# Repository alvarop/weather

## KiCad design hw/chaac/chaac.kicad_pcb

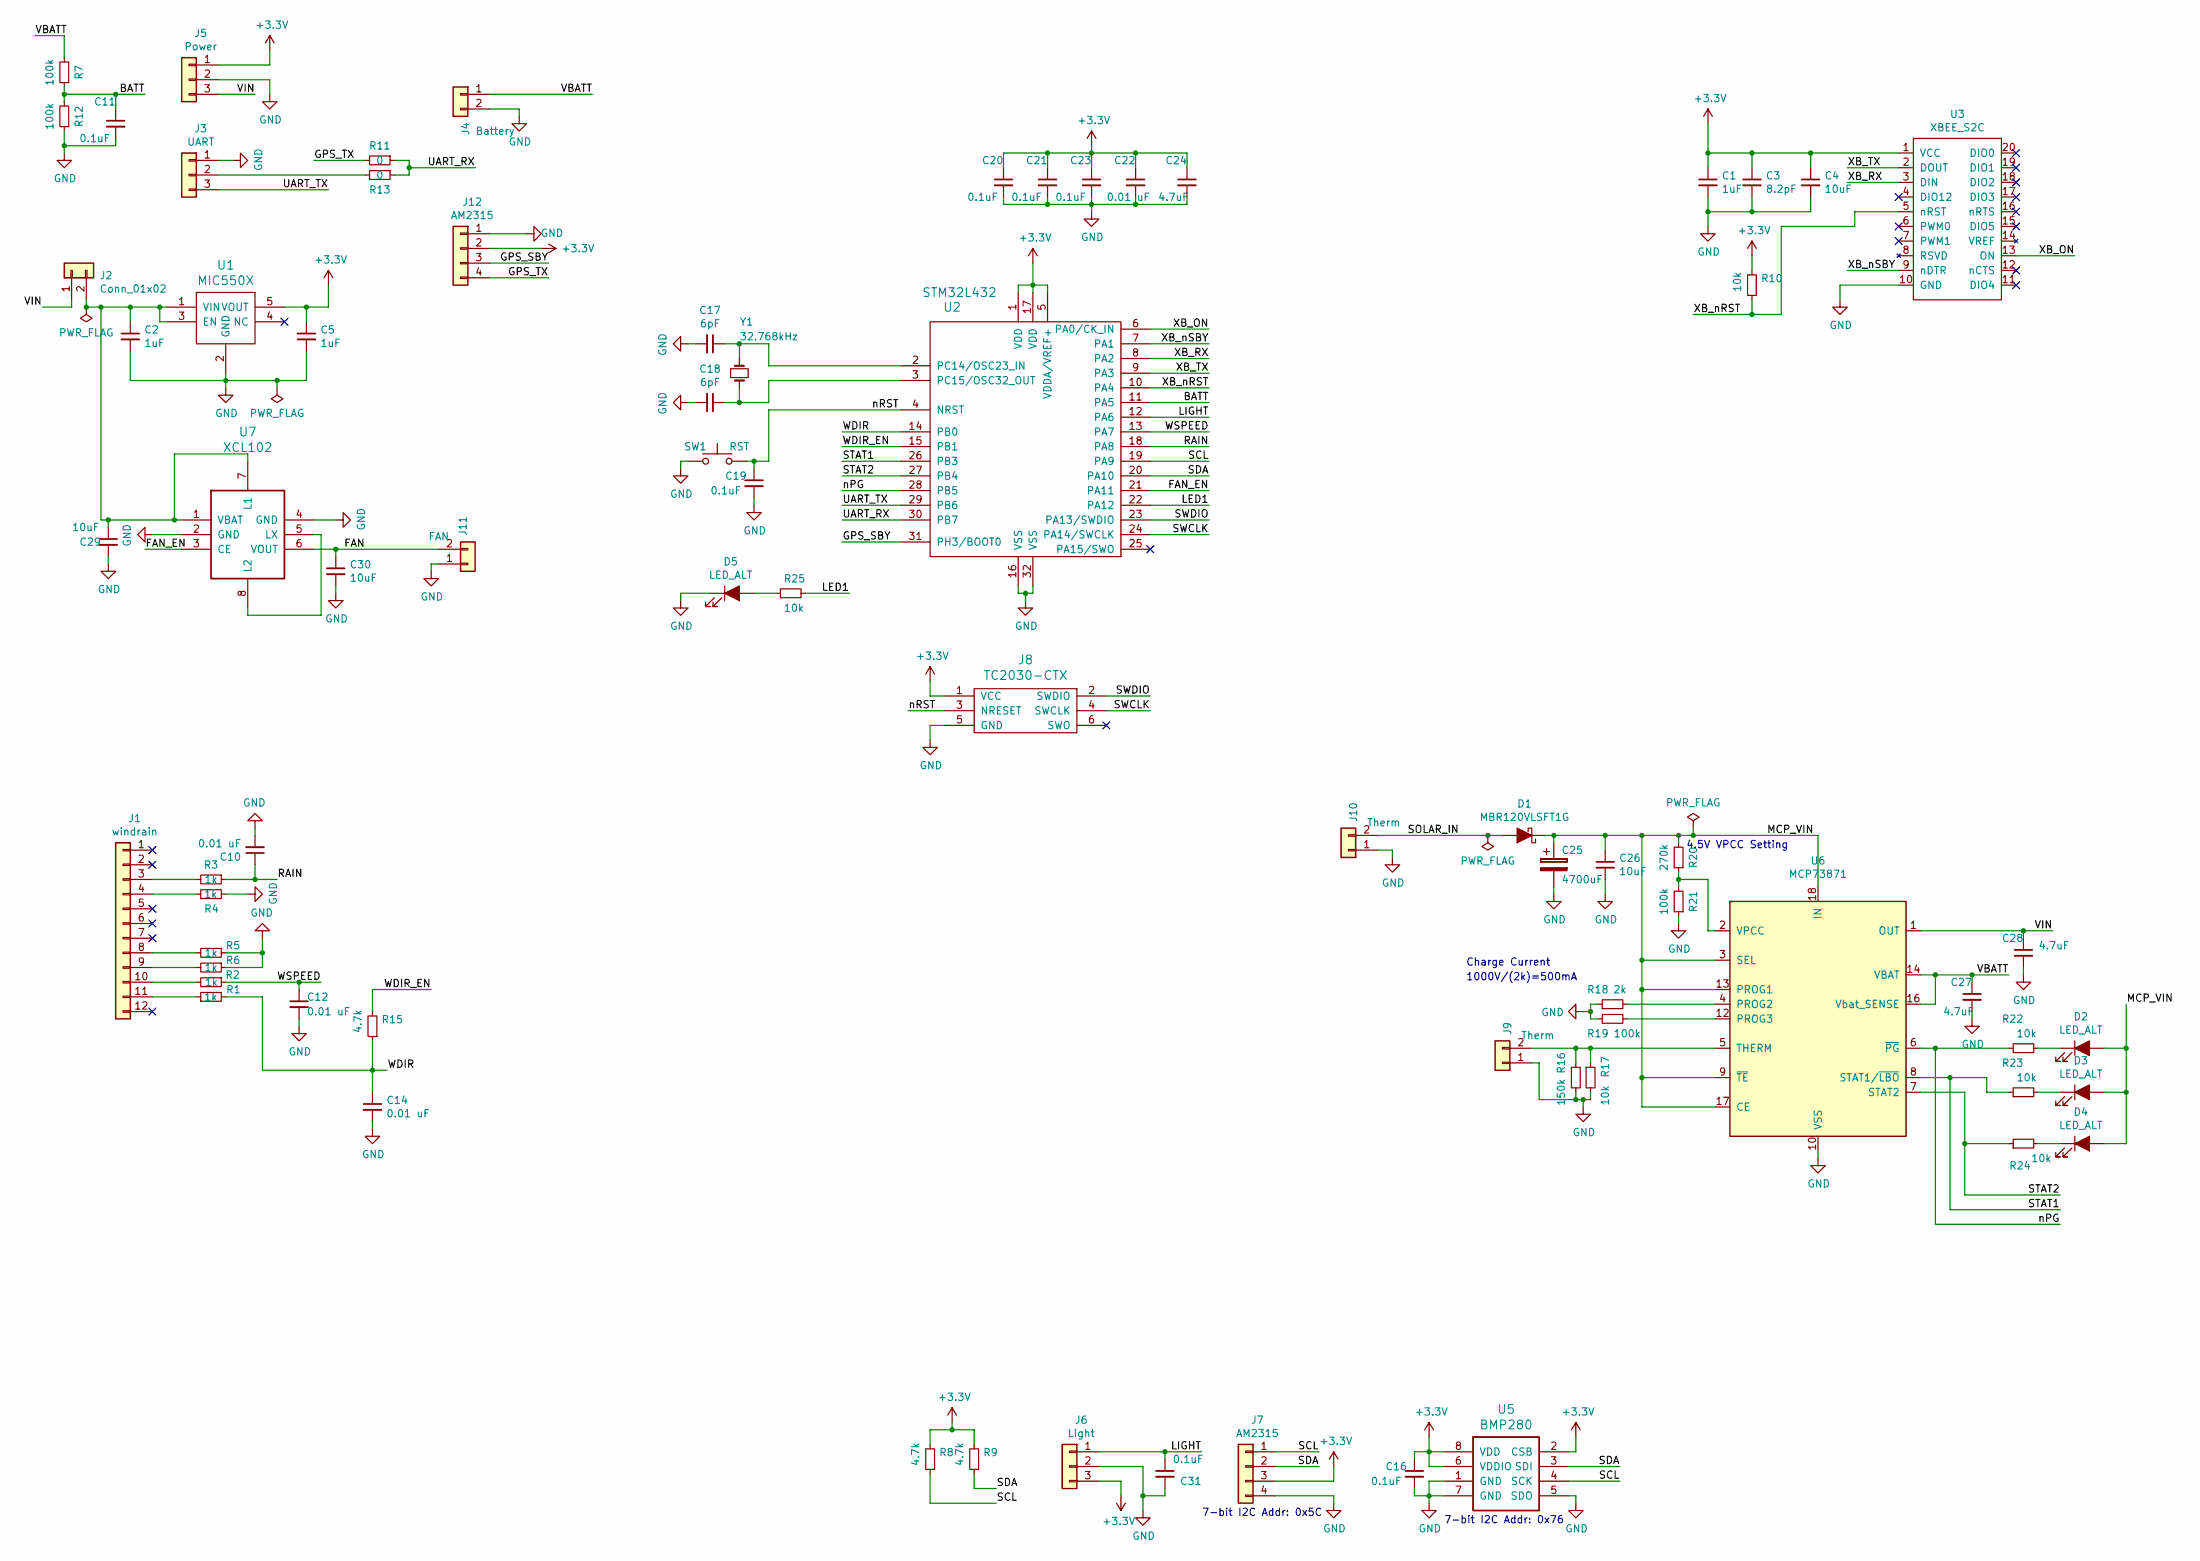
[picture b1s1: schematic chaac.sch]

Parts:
C1, C2, C5: 1uF; C_0603_1608Metric; MPN GRM188R61C105KA93D
C3: 8.2pF; C_0603_1608Metric; MPN CL10C8R2DB8NNNC
C4: 10uF; C_0603_1608Metric; MPN GRM188R60J106ME47D
C10, C12, C14, C22: 0.01 uF; C_0603_1608Metric; MPN CC0603KRX7R9BB103
C11, C16, C19, C20, C21, C23, C31: 0.1uF; C_0603_1608Metric; MPN GRM188R71C104KA01D
C17, C18: 6pF; C_0603_1608Metric
C24, C27, C28: 4.7uF; C_0603_1608Metric
C25: 4700uF; CP_Elec_18x16.5
C26, C29, C30: 10uF; C_0805_2012Metric; MPN GRM21BR61C106KE15K
D1: MBR120VLSFT1G; D_SOD-123F
D2, D3, D4, D5: LED_ALT; LED_0603_1608Metric
J1: windrain; 043814-6621; MPN 0438146621
J2: Conn_01x02; PinHeader_1x02_P2.54mm_Vertical
J3: UART; PinHeader_1x03_P2.54mm_Vertical
J4: Battery; S2B-PH-SM4-TB; MPN S2B-PH-SM4-TB(LF)(SN)
J5: Power; PinHeader_1x03_P2.54mm_Vertical
J6: Light; PinHeader_1x03_P2.54mm_Vertical
J7, J12: AM2315; PinHeader_1x04_P2.54mm_Vertical
J8: TC2030-CTX; TC2030-NL
J9, J10: Therm; PinHeader_1x02_P2.54mm_Vertical
J11: FAN; PinHeader_1x02_P2.54mm_Vertical
R1, R2, R3, R4, R5, R6: 1k; R_0603_1608Metric; MPN RC0603FR-071KL
R7, R12, R19, R21: 100k; R_0603_1608Metric
R8, R9, R15: 4.7k; R_0603_1608Metric; MPN RC0603JR-074K7L
R10, R17, R22, R23, R24, R25: 10k; R_0603_1608Metric; MPN RC0603FR-0710KL
R11, R13: 0; R_0603_1608Metric
R16: 150k; R_0603_1608Metric
R18: 2k; R_0603_1608Metric
R20: 270k; R_0603_1608Metric
SW1: RST; PTS645SM43SMTR92
U1: MIC550X; SOT-23(M5); MPN MIC5504-3.3YM5-TR
U2: STM32L432; UFQFPN32
U3: XBEE_S2C; XBEE_S2C_TH; MPN 366
U5: BMP280; MPN BMP280
U6: MCP73871
U7: XCL102
Y1: 32.768kHz; Crystal_SMD_3215-2Pin_3.2x1.5mm

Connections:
+3V3: C1.1, C3.1, C4.1, C5.1, C16.1, C20.1, C21.1, C22.1, C23.1, C24.1, J5.1, J6.3, J7.3, J8.1 (VCC), J12.2, R8.2, R9.2, R10.2, U1.5 (VOUT), U2.1 (VDD), U2.5 (VDDA/VREF+), U2.17 (VDD), U3.1 (VCC), U5.2 (CSB), U5.6 (VDDIO), U5.8 (VDD)
/BATT: C11.1, R7.1, R12.2, U2.11 (PA5)
/FAN: C30.1, J11.2, U7.6 (VOUT)
/FAN_EN: U2.21 (PA11), U7.3 (CE)
/GPS_SBY: J12.3, U2.31 (PH3/BOOT0)
/GPS_TX: J12.4, R11.2
/LED1: R25.2, U2.22 (PA12)
/LIGHT: C31.1, J6.1, U2.12 (PA6)
/MCP_VIN: C25.1, C26.1, D1.1 (K), D2.2 (A), D3.2 (A), D4.2 (A), R20.2, U6.3 (SEL), U6.9 (~TE), U6.13 (PROG1), U6.17 (CE), U6.18 (IN), U6.19 (IN)
/RAIN: C10.1, R3.1, U2.18 (PA8)
/SCL: J7.1, R8.1, U2.19 (PA9), U5.4 (SCK)
/SDA: J7.2, R9.1, U2.20 (PA10), U5.3 (SDI)
/SOLAR_IN: D1.2 (A), J10.2
/STAT1: R23.1, U2.26 (PB3), U6.8 (STAT1/~LBO~)
/STAT2: R24.1, U2.27 (PB4), U6.7 (STAT2)
/SWCLK: J8.4 (SWCLK), U2.24 (PA14/SWCLK)
/SWDIO: J8.2 (SWDIO), U2.23 (PA13/SWDIO)
/UART_RX: R11.1, R13.1, U2.30 (PB7)
/UART_TX: J3.3, U2.29 (PB6)
/VBATT: C27.1, J4.1, R7.2, U6.14 (VBAT), U6.15 (VBAT), U6.16 (Vbat_SENSE)
/VIN: C28.1, J2.1, J5.3, U6.1 (OUT), U6.20 (OUT)
/WDIR: C14.1, R1.2, R15.1, U2.14 (PB0)
/WDIR_EN: R15.2, U2.15 (PB1)
/WSPEED: C12.1, R2.1, U2.13 (PA7)
/XB_ON: U2.6 (PA0/CK_IN), U3.13 (ON)
/XB_RX: U2.8 (PA2), U3.3 (DIN)
/XB_TX: U2.9 (PA3), U3.2 (DOUT)
/XB_nRST: R10.1, U2.10 (PA4), U3.5 (nRST)
/XB_nSBY: U2.7 (PA1), U3.9 (nDTR)
/nPG: R22.1, U2.28 (PB5), U6.6 (~PG~)
/nRST: C19.1, J8.3 (NRESET), SW1.2, U2.4 (NRST)
GND: C1.2, C2.2, C3.2, C4.2, C5.2, C10.2, C11.2, C12.2, C14.2, C16.2, C17.2, C18.2, C19.2, C20.2, C21.2, C22.2, C23.2, C24.2, C25.2, C26.2, C27.2, C28.2, C29.2, C30.2, C31.2, D5.1 (K), J3.1, J4.2, J5.2, J6.2, J7.4, J8.5 (GND), J9.1, J10.1, J11.1, J12.1, R4.2, R5.1, R6.1, R12.1, R16.2, R17.2, R18.1, R19.1, R21.1, SW1.1, U1.2 (GND), U2.16 (VSS), U2.32 (VSS), U3.10 (GND), U5.1 (GND), U5.5 (SDO), U5.7 (GND), U6.10 (VSS), U6.11 (VSS), U6.21 (VSS), U7.2 (GND), U7.4 (GND)
unnamed: C2.1, C29.1, J2.2, U1.1 (VIN), U1.3 (EN), U7.1 (VBAT), U7.7 (L1)
unnamed: C17.1, U2.2 (PC14/OSC23_IN), Y1.1
unnamed: C18.1, U2.3 (PC15/OSC32_OUT), Y1.2
unnamed: D2.1 (K), R22.2
unnamed: D3.1 (K), R23.2
unnamed: D4.1 (K), R24.2
unnamed: D5.2 (A), R25.1
unnamed: J1.3, R3.2
unnamed: J1.4, R4.1
unnamed: J1.8, R5.2
unnamed: J1.9, R6.2
unnamed: J1.10, R2.2
unnamed: J1.11, R1.1
unnamed: J3.2, R13.2
unnamed: J9.2, R16.1, R17.1, U6.5 (THERM)
unnamed: R18.2, U6.4 (PROG2)
unnamed: R19.2, U6.12 (PROG3)
unnamed: R20.1, R21.2, U6.2 (VPCC)
unnamed: U7.5 (LX), U7.8 (L2)

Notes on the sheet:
7-bit I2C Addr: 0x76
7-bit I2C Addr: 0x5C
4.5V VPCC Setting
Charge Current
1000V/(2k)=500mA

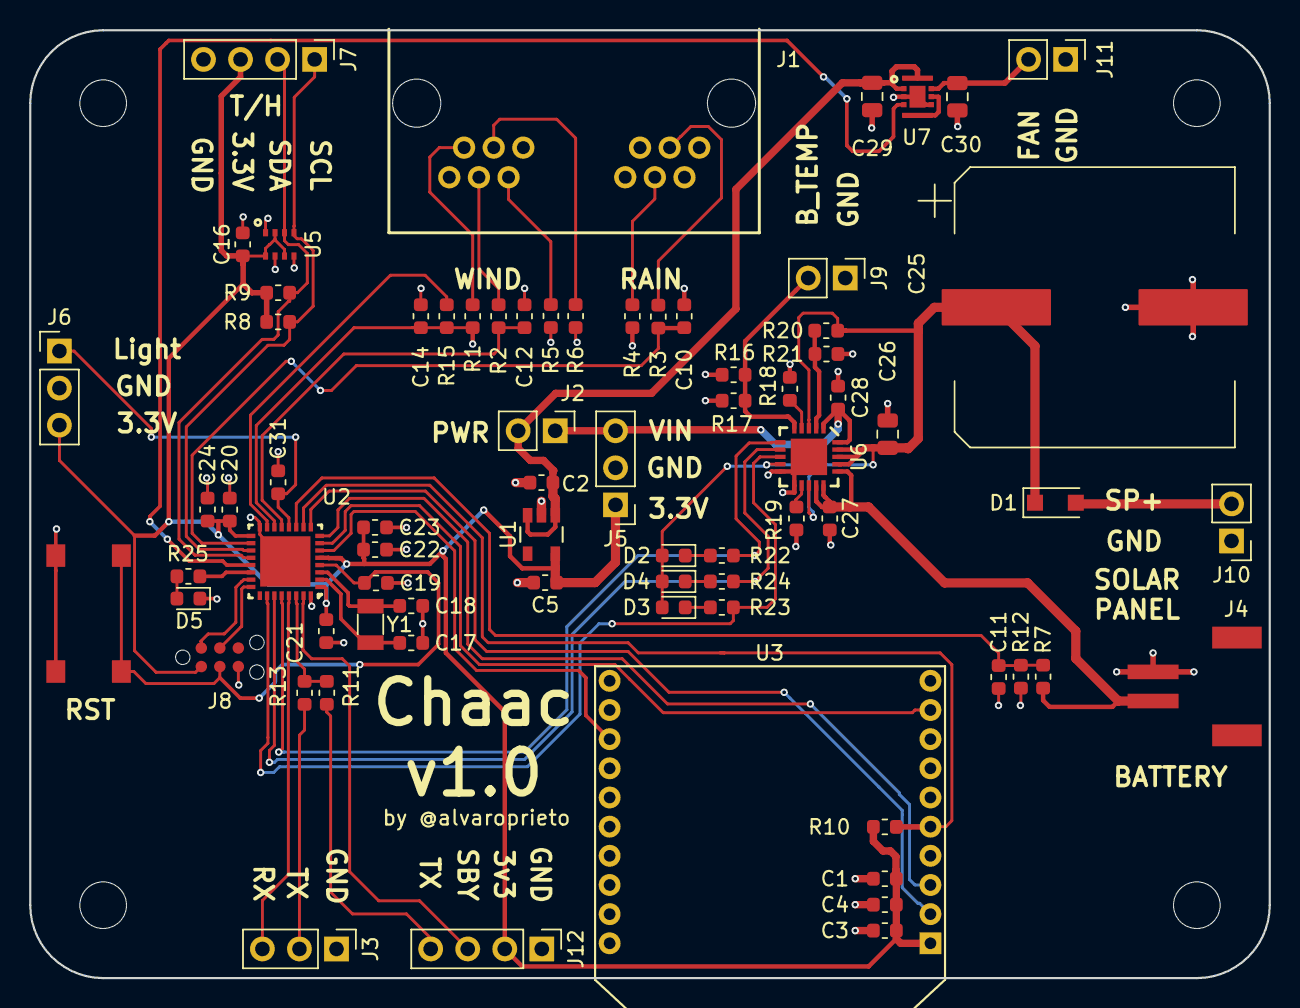
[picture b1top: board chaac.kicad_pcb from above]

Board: 2 copper layers, 85.0 x 65.0 mm, 74 parts (0 on the bottom side), 51 nets.

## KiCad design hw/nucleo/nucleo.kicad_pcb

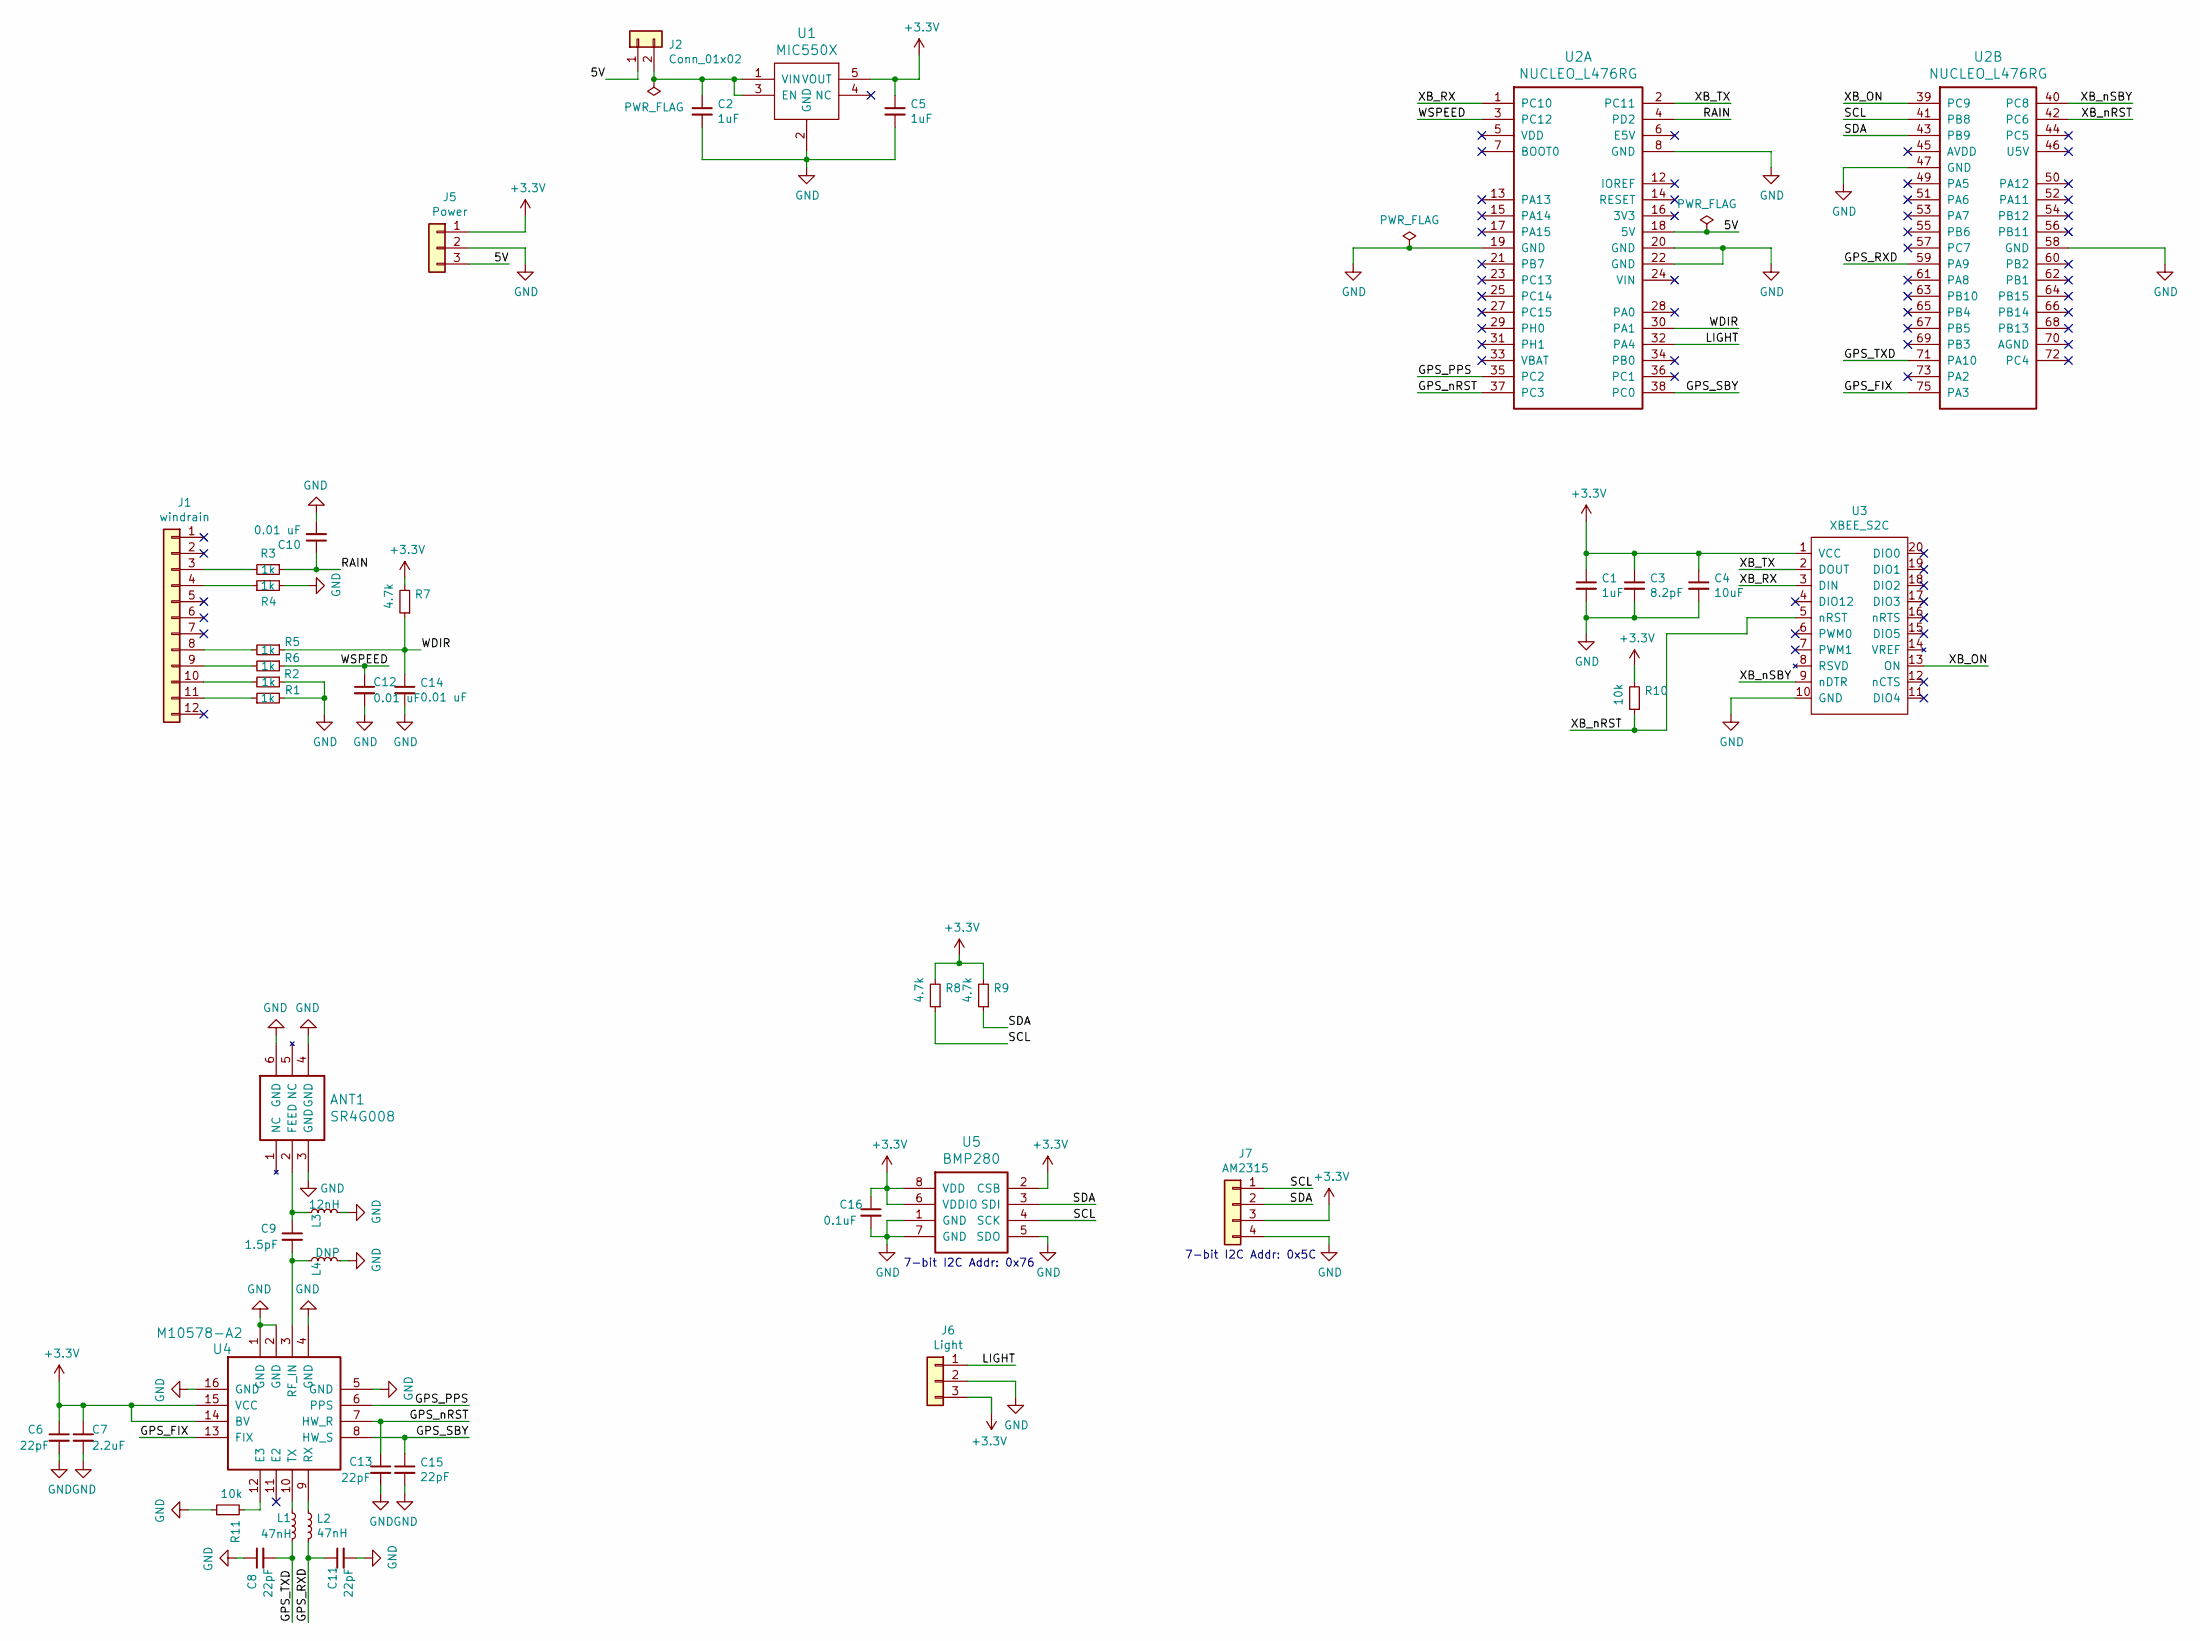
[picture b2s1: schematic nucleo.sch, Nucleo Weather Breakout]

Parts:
ANT1: SR4G008; MPN SR4G008
C1, C2, C5: 1uF; C_0603_1608Metric; MPN GRM188R61C105KA93D
C3: 8.2pF; C_0603_1608Metric; MPN CL10C8R2DB8NNNC
C4: 10uF; C_0603_1608Metric; MPN GRM188R60J106ME47D
C6, C8, C11, C13, C15: 22pF; C_0603_1608Metric; MPN CL10C220JB8NFNC
C7: 2.2uF; C_0603_1608Metric; MPN CL10A225KP8NNNC
C9: 1.5pF; C_0402_1005Metric; MPN ‎GJM1555C1H1R5CB01D‎
C10, C12, C14: 0.01 uF; C_0603_1608Metric; MPN CC0603KRX7R9BB103
C16: 0.1uF; C_0603_1608Metric; MPN GRM188R71C104KA01D
J1: windrain; 043814-6621; MPN 0438146621
J2: Conn_01x02; PinHeader_1x02_P2.54mm_Vertical
J5: Power; PinHeader_1x03_P2.54mm_Vertical
J6: Light; PinHeader_1x03_P2.54mm_Vertical
J7: AM2315; PinHeader_1x04_P2.54mm_Vertical
L1, L2: 47nH; L_0603_1608Metric; MPN ‎L-14C47NJV4T
L3: 12nH; L_0402_1005Metric; MPN ‎LQG15HS12NJ02D‎
L4: DNP; L_0402_1005Metric
R1, R2, R3, R4, R5, R6: 1k; R_0603_1608Metric; MPN RC0603FR-071KL
R7, R8, R9: 4.7k; R_0603_1608Metric; MPN RC0603JR-074K7L
R10, R11: 10k; R_0603_1608Metric; MPN RC0603FR-0710KL
U1: MIC550X; SOT-23(M5); MPN MIC5504-3.3YM5-TR
U2: NUCLEO_L476RG; MPN CES-119-01-T-D
U3: XBEE_S2C; XBEE_S2C_TH; MPN 366
U4: M10578-A2; MPN M10578-A2
U5: BMP280; MPN BMP280

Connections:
+3V3: C1.1, C3.1, C4.1, C5.1, C6.1, C7.1, C16.1, J5.1, J6.3, J7.3, R7.2, R8.2, R9.2, R10.2, U1.5 (VOUT), U3.1 (VCC), U4.14 (BV), U4.15 (VCC), U5.2 (CSB), U5.6 (VDDIO), U5.8 (VDD)
/5V: J2.1, J5.3, U2.18 (5V); also elsewhere on the board
/GPS_FIX: U2.75 (PA3), U4.13 (FIX); also elsewhere on the board
/GPS_PPS: U2.35 (PC2), U4.6 (PPS); also elsewhere on the board
/GPS_RXD: C11.1, L2.2, U2.59 (PA9); also elsewhere on the board
/GPS_SBY: C15.1, U2.38 (PC0), U4.8 (HW_S); also elsewhere on the board
/GPS_TXD: C8.2, L1.2, U2.71 (PA10); also elsewhere on the board
/GPS_nRST: C13.1, U2.37 (PC3), U4.7 (HW_R); also elsewhere on the board
/LIGHT: J6.1, U2.32 (PA4); also elsewhere on the board
/RAIN: C10.1, R3.1, U2.4 (PD2); also elsewhere on the board
/SCL: J7.1, R8.1, U2.41 (PB8), U5.4 (SCK); also elsewhere on the board
/SDA: J7.2, R9.1, U2.43 (PB9), U5.3 (SDI); also elsewhere on the board
/WDIR: C14.1, R5.1, R7.1, U2.30 (PA1); also elsewhere on the board
/WSPEED: C12.1, R6.1, U2.3 (PC12); also elsewhere on the board
/XB_ON: U2.39 (PC9), U3.13 (ON); also elsewhere on the board
/XB_RX: U2.1 (PC10), U3.3 (DIN); also elsewhere on the board
/XB_TX: U2.2 (PC11), U3.2 (DOUT); also elsewhere on the board
/XB_nRST: R10.1, U2.42 (PC6), U3.5 (nRST); also elsewhere on the board
/XB_nSBY: U2.40 (PC8), U3.9 (nDTR); also elsewhere on the board
GND: ANT1.3 (GND), ANT1.4 (GND), ANT1.6 (GND), C1.2, C2.2, C3.2, C4.2, C5.2, C6.2, C7.2, C8.1, C10.2, C11.2, C12.2, C13.2, C14.2, C15.2, C16.2, J5.2, J6.2, J7.4, L3.2, L4.2, R1.2, R2.1, R4.2, R11.1, U1.2 (GND), U2.8 (GND), U2.19 (GND), U2.20 (GND), U2.22 (GND), U2.47 (GND), U2.58 (GND), U3.10 (GND), U4.1 (GND), U4.2 (GND), U4.4 (GND), U4.5 (GND), U4.16 (GND), U5.1 (GND), U5.5 (SDO), U5.7 (GND); also elsewhere on the board
unnamed: ANT1.2 (FEED), C9.1, L3.1
unnamed: C2.1, J2.2, U1.1 (VIN), U1.3 (EN)
unnamed: C9.2, L4.1, U4.3 (RF_IN)
unnamed: J1.3, R3.2
unnamed: J1.4, R4.1
unnamed: J1.8, R5.2
unnamed: J1.9, R6.2
unnamed: J1.10, R2.2
unnamed: J1.11, R1.1
unnamed: L1.1, U4.10 (TX)
unnamed: L2.1, U4.9 (RX)
unnamed: R11.2, U4.12 (E3)
unnamed 41: U2.5 (VDD); also elsewhere on the board
unnamed 42: U2.6 (E5V); also elsewhere on the board
unnamed 43: U2.7 (BOOT0); also elsewhere on the board
unnamed 44: U2.9 (NC); also elsewhere on the board
unnamed 45: U2.10 (NC); also elsewhere on the board
unnamed 46: U2.11 (NC); also elsewhere on the board
unnamed 47: U2.12 (IOREF); also elsewhere on the board
unnamed 48: U2.13 (PA13); also elsewhere on the board
unnamed 49: U2.14 (RESET); also elsewhere on the board
unnamed 50: U2.15 (PA14); also elsewhere on the board
unnamed 51: U2.16 (3V3); also elsewhere on the board
unnamed 52: U2.17 (PA15); also elsewhere on the board
unnamed 53: U2.21 (PB7); also elsewhere on the board
unnamed 54: U2.23 (PC13); also elsewhere on the board
unnamed 55: U2.24 (VIN); also elsewhere on the board
unnamed 56: U2.25 (PC14); also elsewhere on the board
unnamed 57: U2.26 (NC); also elsewhere on the board
unnamed 58: U2.27 (PC15); also elsewhere on the board
unnamed 59: U2.28 (PA0); also elsewhere on the board
unnamed 60: U2.29 (PH0); also elsewhere on the board
unnamed 61: U2.31 (PH1); also elsewhere on the board
unnamed 62: U2.33 (VBAT); also elsewhere on the board
unnamed 63: U2.34 (PB0); also elsewhere on the board
unnamed 64: U2.36 (PC1); also elsewhere on the board
unnamed 65: U2.44 (PC5); also elsewhere on the board
unnamed 66: U2.45 (AVDD); also elsewhere on the board
unnamed 67: U2.46 (U5V); also elsewhere on the board
unnamed 68: U2.48 (NC); also elsewhere on the board
unnamed 69: U2.49 (PA5); also elsewhere on the board
unnamed 70: U2.50 (PA12); also elsewhere on the board
unnamed 71: U2.51 (PA6); also elsewhere on the board
unnamed 72: U2.52 (PA11); also elsewhere on the board
unnamed 73: U2.53 (PA7); also elsewhere on the board
unnamed 74: U2.54 (PB12); also elsewhere on the board
unnamed 75: U2.55 (PB6); also elsewhere on the board
unnamed 76: U2.56 (PB11); also elsewhere on the board
unnamed 77: U2.57 (PC7); also elsewhere on the board
unnamed 78: U2.60 (PB2); also elsewhere on the board
unnamed 79: U2.61 (PA8); also elsewhere on the board
unnamed 80: U2.62 (PB1); also elsewhere on the board
unnamed 81: U2.63 (PB10); also elsewhere on the board
unnamed 82: U2.64 (PB15); also elsewhere on the board
unnamed 83: U2.65 (PB4); also elsewhere on the board
unnamed 84: U2.66 (PB14); also elsewhere on the board
unnamed 85: U2.67 (PB5); also elsewhere on the board
unnamed 86: U2.68 (PB13); also elsewhere on the board
unnamed 87: U2.69 (PB3); also elsewhere on the board
unnamed 88: U2.70 (AGND); also elsewhere on the board
unnamed 89: U2.72 (PC4); also elsewhere on the board
unnamed 90: U2.73 (PA2); also elsewhere on the board
unnamed 91: U2.74 (NC); also elsewhere on the board
unnamed 92: U2.76 (NC); also elsewhere on the board

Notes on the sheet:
7-bit I2C Addr: 0x76
7-bit I2C Addr: 0x5C

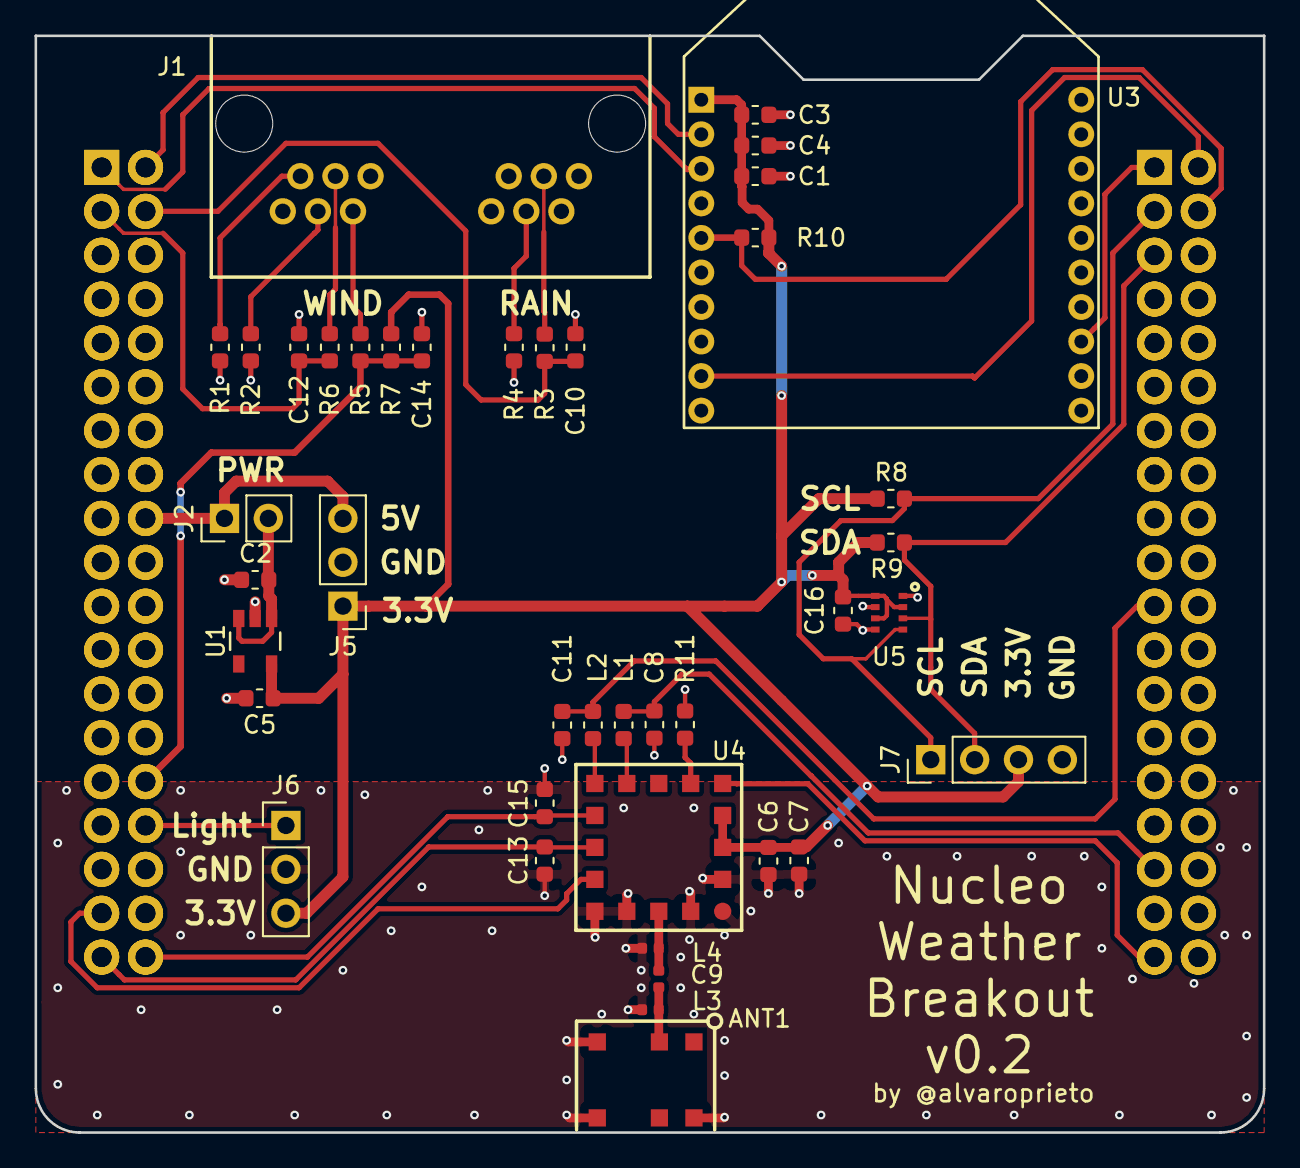
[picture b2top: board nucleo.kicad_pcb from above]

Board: 2 copper layers, 71.1 x 63.5 mm, 43 parts (0 on the bottom side), 84 nets.

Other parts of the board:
U2#2: NUCLEO_L476RG

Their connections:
/5V: U2#2.18; also elsewhere on the board
/GPS_FIX: U2#2.75; also elsewhere on the board
/GPS_PPS: U2#2.35; also elsewhere on the board
/GPS_RXD: U2#2.59; also elsewhere on the board
/GPS_SBY: U2#2.38; also elsewhere on the board
/GPS_TXD: U2#2.71; also elsewhere on the board
/GPS_nRST: U2#2.37; also elsewhere on the board
/LIGHT: U2#2.32; also elsewhere on the board
/RAIN: U2#2.4; also elsewhere on the board
/SCL: U2#2.41; also elsewhere on the board
/SDA: U2#2.43; also elsewhere on the board
/WDIR: U2#2.30; also elsewhere on the board
/WSPEED: U2#2.3; also elsewhere on the board
/XB_ON: U2#2.39; also elsewhere on the board
/XB_RX: U2#2.1; also elsewhere on the board
/XB_TX: U2#2.2; also elsewhere on the board
/XB_nRST: U2#2.42; also elsewhere on the board
/XB_nSBY: U2#2.40; also elsewhere on the board
GND: U2#2.8, U2#2.19, U2#2.20, U2#2.22, U2#2.47, U2#2.58; also elsewhere on the board
unnamed 41: U2#2.5; also elsewhere on the board
unnamed 42: U2#2.6; also elsewhere on the board
unnamed 43: U2#2.7; also elsewhere on the board
unnamed 44: U2#2.9; also elsewhere on the board
unnamed 45: U2#2.10; also elsewhere on the board
unnamed 46: U2#2.11; also elsewhere on the board
unnamed 47: U2#2.12; also elsewhere on the board
unnamed 48: U2#2.13; also elsewhere on the board
unnamed 49: U2#2.14; also elsewhere on the board
unnamed 50: U2#2.15; also elsewhere on the board
unnamed 51: U2#2.16; also elsewhere on the board
unnamed 52: U2#2.17; also elsewhere on the board
unnamed 53: U2#2.21; also elsewhere on the board
unnamed 54: U2#2.23; also elsewhere on the board
unnamed 55: U2#2.24; also elsewhere on the board
unnamed 56: U2#2.25; also elsewhere on the board
unnamed 57: U2#2.26; also elsewhere on the board
unnamed 58: U2#2.27; also elsewhere on the board
unnamed 59: U2#2.28; also elsewhere on the board
unnamed 60: U2#2.29; also elsewhere on the board
unnamed 61: U2#2.31; also elsewhere on the board
unnamed 62: U2#2.33; also elsewhere on the board
unnamed 63: U2#2.34; also elsewhere on the board
unnamed 64: U2#2.36; also elsewhere on the board
unnamed 65: U2#2.44; also elsewhere on the board
unnamed 66: U2#2.45; also elsewhere on the board
unnamed 67: U2#2.46; also elsewhere on the board
unnamed 68: U2#2.48; also elsewhere on the board
unnamed 69: U2#2.49; also elsewhere on the board
unnamed 70: U2#2.50; also elsewhere on the board
unnamed 71: U2#2.51; also elsewhere on the board
unnamed 72: U2#2.52; also elsewhere on the board
unnamed 73: U2#2.53; also elsewhere on the board
unnamed 74: U2#2.54; also elsewhere on the board
unnamed 75: U2#2.55; also elsewhere on the board
unnamed 76: U2#2.56; also elsewhere on the board
unnamed 77: U2#2.57; also elsewhere on the board
unnamed 78: U2#2.60; also elsewhere on the board
unnamed 79: U2#2.61; also elsewhere on the board
unnamed 80: U2#2.62; also elsewhere on the board
unnamed 81: U2#2.63; also elsewhere on the board
unnamed 82: U2#2.64; also elsewhere on the board
unnamed 83: U2#2.65; also elsewhere on the board
unnamed 84: U2#2.66; also elsewhere on the board
unnamed 85: U2#2.67; also elsewhere on the board
unnamed 86: U2#2.68; also elsewhere on the board
unnamed 87: U2#2.69; also elsewhere on the board
unnamed 88: U2#2.70; also elsewhere on the board
unnamed 89: U2#2.72; also elsewhere on the board
unnamed 90: U2#2.73; also elsewhere on the board
unnamed 91: U2#2.74; also elsewhere on the board
unnamed 92: U2#2.76; also elsewhere on the board

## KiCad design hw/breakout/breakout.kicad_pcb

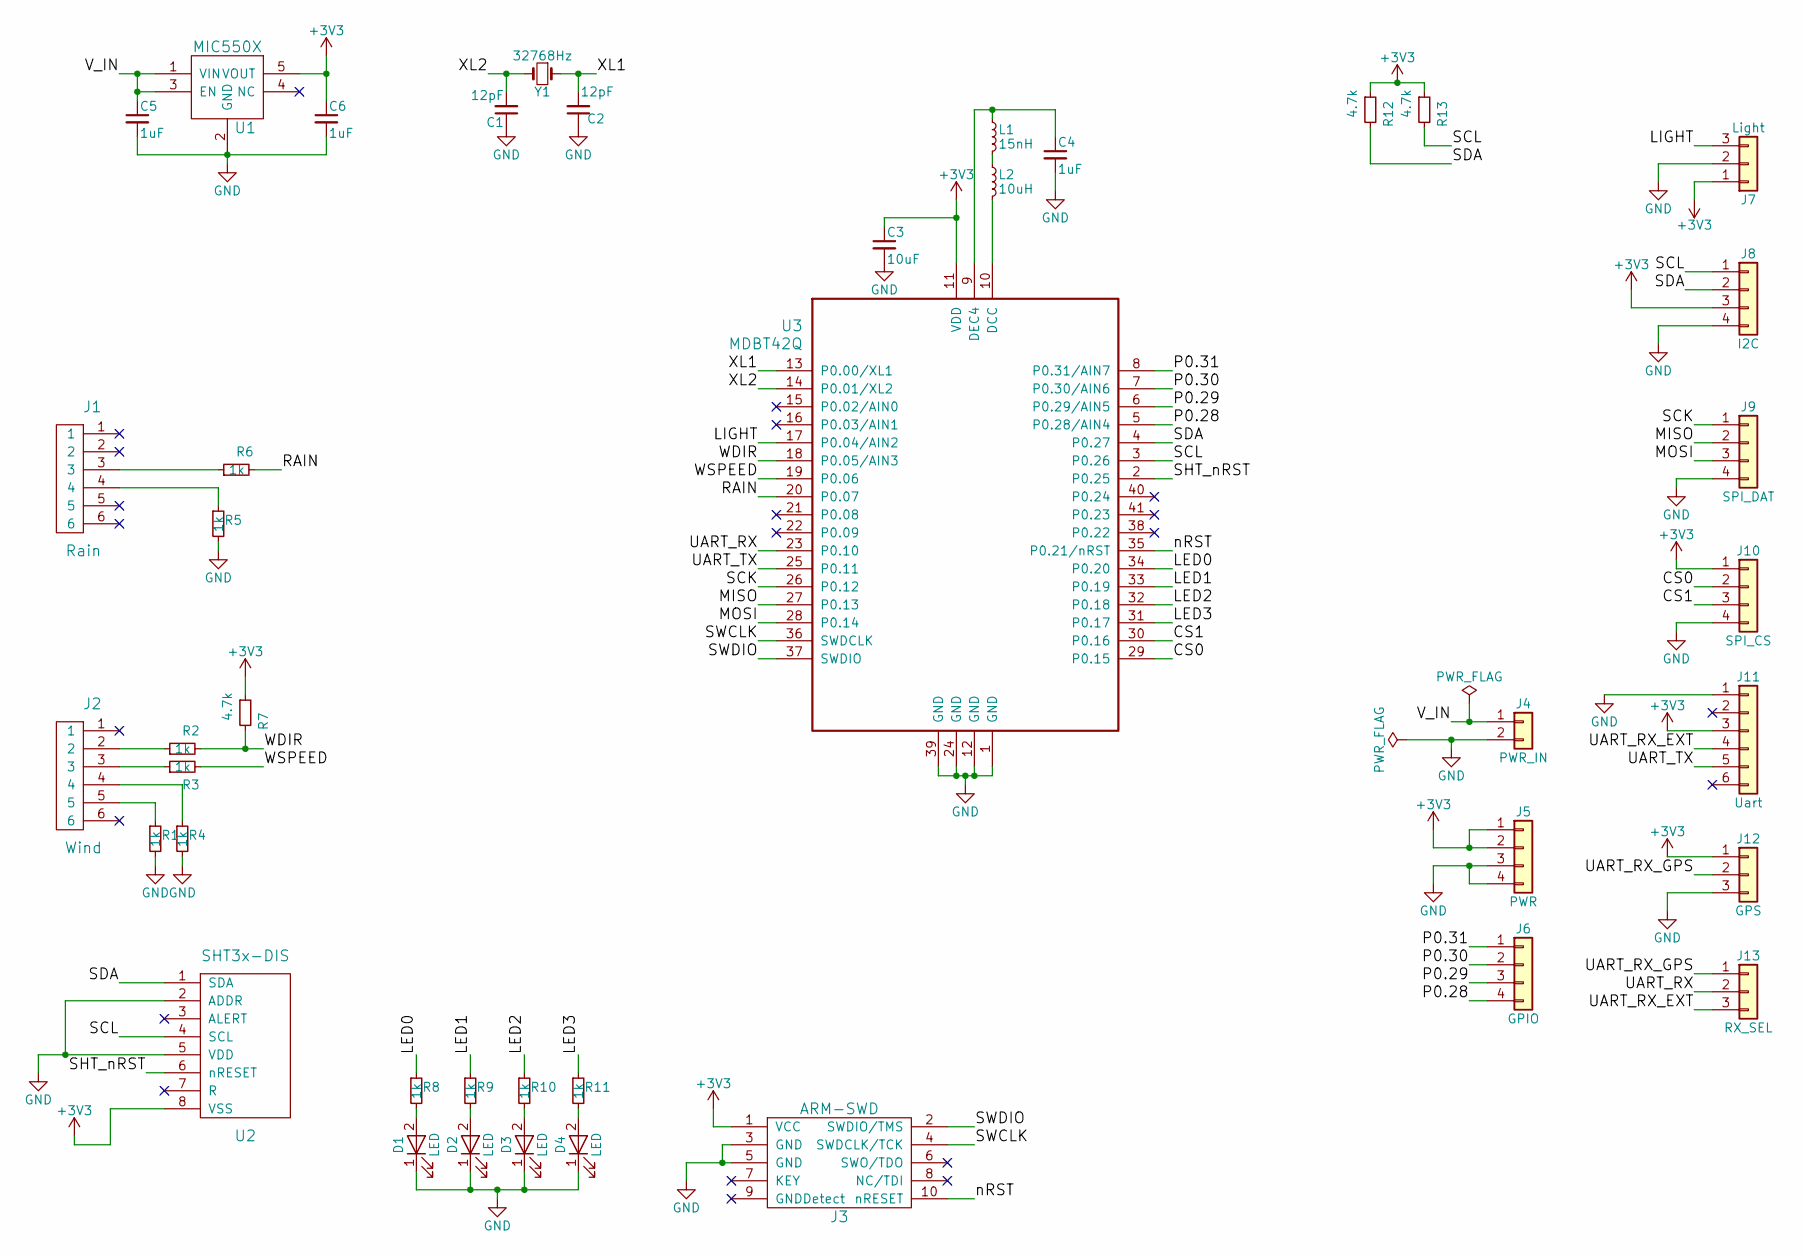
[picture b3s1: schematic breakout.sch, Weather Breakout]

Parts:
C1, C2: 12pF; C_0603; MPN CL10C120FB8NNNC
C3: 10uF; C_0603; MPN GRM188R60J106ME47D
C4, C5, C6: 1uF; C_0603; MPN CL10A105MQ8NNNC
D1, D2, D3, D4: LED; LED_0603; MPN LTST-C190GKT
J1: Rain; RJ11; MPN A-2004-1-4-LP-N-R
J2: Wind; RJ11; MPN A-2004-1-4-LP-N-R
J3: ARM-SWD; ARM_SWD_SMD; MPN 20021121-00010C4LF
J4: PWR_IN; Pin_Header_Straight_1x02_Pitch2.54mm
J5: PWR; Pin_Header_Straight_1x04_Pitch2.54mm
J6: GPIO; Pin_Header_Straight_1x04_Pitch2.54mm
J7: Light; Pin_Header_Straight_1x03_Pitch2.54mm
J8: I2C; Pin_Header_Straight_1x04_Pitch2.54mm
J9: SPI_DAT; Pin_Header_Straight_1x04_Pitch2.54mm
J10: SPI_CS; Pin_Header_Straight_1x04_Pitch2.54mm
J11: Uart; Pin_Header_Straight_1x06_Pitch2.54mm
J12: GPS; Pin_Header_Straight_1x03_Pitch2.54mm
J13: RX_SEL; Pin_Header_Straight_1x03_Pitch2.54mm
L1: 15nH; R_0603; MPN HK160815NJ-T
L2: 10uH; R_0603; MPN LBMF1608T100K
R1, R2, R3, R4, R5, R6, R8, R9, R10, R11: 1k; R_0603; MPN RC0603JR-071KL
R7, R12, R13: 4.7k; R_0603; MPN RC0603JR-074K7L
U1: MIC550X; SOT-23(M5); MPN MIC5504-3.3YM5-TR
U2: SHT3x-DIS; SHT3x; MPN SHT31-DIS-F2.5KS
U3: MDBT42Q; MPN 317030213
Y1: 32768Hz; FC-135; MPN FC-135 32.7680KA-AC0

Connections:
+3V3: C3.1, C6.1, J3.1 (VCC), J5.1, J5.2, J7.1, J8.3, J10.1, J11.3, J12.1, R7.1, R12.1, R13.1, U1.5 (VOUT), U2.8 (VSS), U3.11 (VDD)
/CS0: J10.2, U3.29 (P0.15)
/CS1: J10.3, U3.30 (P0.16)
/LED0: R8.1, U3.34 (P0.20)
/LED1: R9.1, U3.33 (P0.19)
/LED2: R10.1, U3.32 (P0.18)
/LED3: R11.1, U3.31 (P0.17)
/LIGHT: J7.3, U3.17 (P0.04/AIN2)
/MISO: J9.2, U3.27 (P0.13)
/MOSI: J9.3, U3.28 (P0.14)
/P0.28: J6.4, U3.5 (P0.28/AIN4)
/P0.29: J6.3, U3.6 (P0.29/AIN5)
/P0.30: J6.2, U3.7 (P0.30/AIN6)
/P0.31: J6.1, U3.8 (P0.31/AIN7)
/RAIN: R6.2, U3.20 (P0.07)
/SCK: J9.1, U3.26 (P0.12)
/SCL: J8.1, R13.2, U2.4 (SCL), U3.3 (P0.26)
/SDA: J8.2, R12.2, U2.1 (SDA), U3.4 (P0.27)
/SHT_nRST: U2.6 (nRESET), U3.2 (P0.25)
/SWCLK: J3.4 (SWDCLK/TCK), U3.36 (SWDCLK)
/SWDIO: J3.2 (SWDIO/TMS), U3.37 (SWDIO)
/UART_RX: J13.2, U3.23 (P0.10)
/UART_RX_EXT: J11.4, J13.3
/UART_RX_GPS: J12.2, J13.1
/UART_TX: J11.5, U3.25 (P0.11)
/V_IN: C5.1, J4.1, U1.1 (VIN), U1.3 (EN)
/WDIR: R2.2, R7.2, U3.18 (P0.05/AIN3)
/WSPEED: R3.2, U3.19 (P0.06)
/XL1: C2.2, U3.13 (P0.00/XL1), Y1.1
/XL2: C1.2, U3.14 (P0.01/XL2), Y1.2
/nRST: J3.10 (nRESET), U3.35 (P0.21/nRST)
GND: C1.1, C2.1, C3.2, C4.2, C5.2, C6.2, D1.1 (K), D2.1 (K), D3.1 (K), D4.1 (K), J3.3 (GND), J3.5 (GND), J4.2, J5.3, J5.4, J7.2, J8.4, J9.4, J10.4, J11.1, J12.3, R1.2, R4.2, R5.2, U1.2 (GND), U2.2 (ADDR), U2.5 (VDD), U3.1 (GND), U3.12 (GND), U3.24 (GND), U3.39 (GND)
unnamed: C4.1, L1.1, U3.9 (DEC4)
unnamed: D1.2 (A), R8.2
unnamed: D2.2 (A), R9.2
unnamed: D3.2 (A), R10.2
unnamed: D4.2 (A), R11.2
unnamed: J1.3, R6.1
unnamed: J1.4, R5.1
unnamed: J2.2, R2.1
unnamed: J2.3, R3.1
unnamed: J2.4, R4.1
unnamed: J2.5, R1.1
unnamed: L1.2, L2.1
unnamed: L2.2, U3.10 (DCC)
